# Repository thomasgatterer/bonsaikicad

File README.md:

# bonsaikicad

Hier die (pädagogisch vereinfachte) Simulation des Lerncomputers:
https://bonsai.pinyto.de/

Und hier die Seite des Lehrers der das Projekt ins Leben gerufen hat (ist übrigens der Vater vom Programmierer der Simulation):
http://www.hsg-kl.de/faecher/inf/material/bonsai/

Weiterführendes:
https://tams-www.informatik.uni-hamburg.de/applets/baukasten/DA/VNR_Einleitung.html
www.saar.de/~awa/data/Von-Neumann-Rechner.pdf
informatik-erleben.aau.at/einheiten/uebersicht.php?id0d3

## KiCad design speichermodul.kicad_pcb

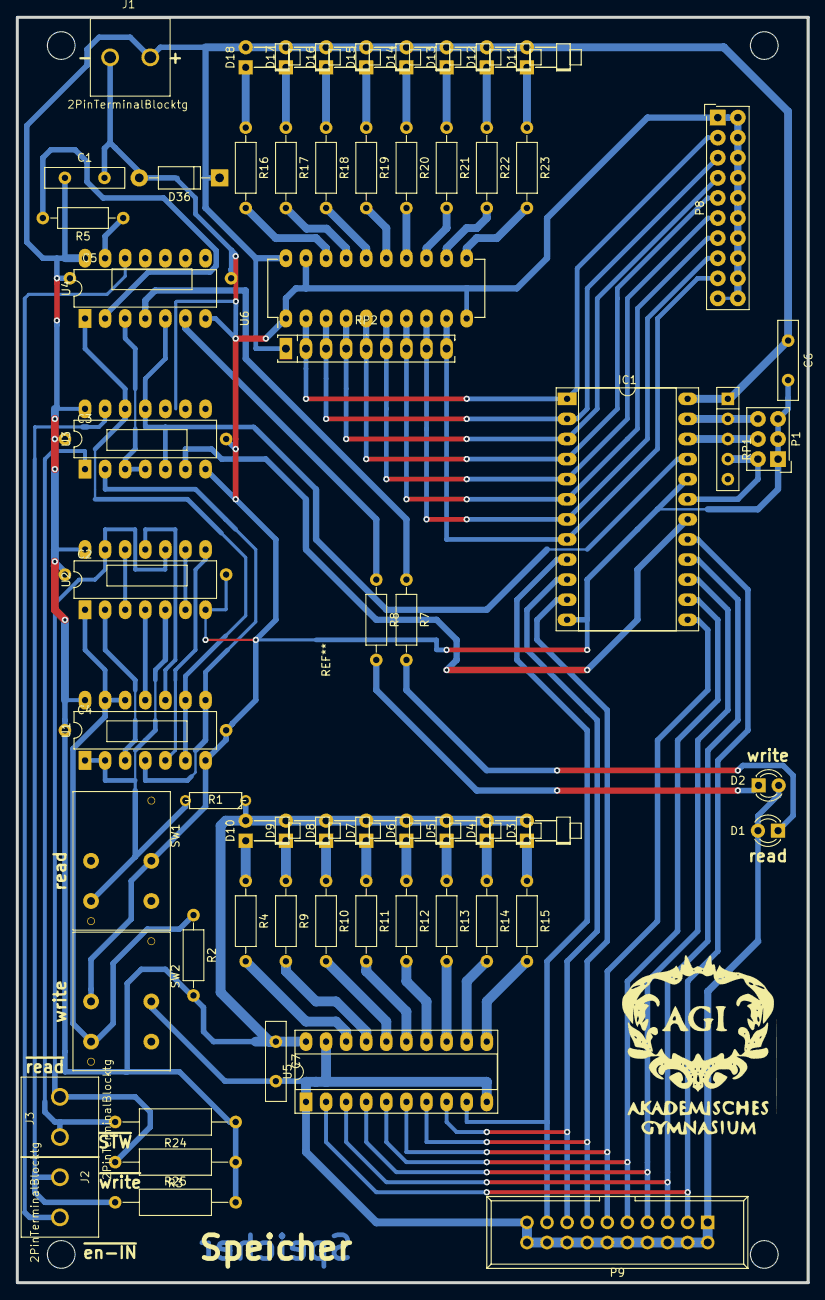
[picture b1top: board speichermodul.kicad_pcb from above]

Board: 2 copper layers, 100.0 x 160.0 mm, 67 parts (0 on the bottom side), 76 nets.

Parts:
C1, C6, C7: 100n; C_Disc_D10.0mm_W2.5mm_P5.00mm
C2, C3, C4, C5: 100n; yyDisc_D10.0mm_W2.5mm_P.00mm
D1, D2: LED; LED_D3.0mm
D3, D4, D5, D6, D7, D8, D9, D10, D11, D12, D13, D14, D15, D16, D17, D18: LED; LED_D1.8mm_W1.8mm_H2.4mm_Horizontal_O3.81mm_Z8.2mm
D36: D; D_DO-41_SOD81_P10.16mm_Horizontal
IC1: 6116; DIP-24_W15.24mm_Socket_LongPads
J1, J2, J3: 2PinTerminalBlocktg
P1: CONN_3X2; SDL-106-X-XX_2x03
P8: CONN_02X10; SDL-120-X-XX_2x10
P9: CONN_02X10; IDC_Header_Straight_20pins
R1: 1,7k; R3
R2: 4,7k; R_Axial_DIN0207_L6.3mm_D2.5mm_P10.16mm_Horizontal
R3, R24, R25: 4,7k; R_Axial_DIN0309_L9.0mm_D3.2mm_P15.24mm_Horizontal
R4, R9, R10, R11, R12, R13, R14, R15, R16, R17, R18, R19, R20, R21, R22, R23: 330; R_Axial_DIN0207_L6.3mm_D2.5mm_P10.16mm_Horizontal
R5: 0; R_Axial_DIN0207_L6.3mm_D2.5mm_P10.16mm_Horizontal
R7, R8: R; R_Axial_DIN0207_L6.3mm_D2.5mm_P10.16mm_Horizontal
RP1: R_PACK4BUSSED; R_Array_SIP5
RP2: R_PACK8BUSSED; SIP9_Housing_BigPads
SW1, SW2: SW_PUSH-tg; SW_PUSH_LCD_E3_SAxxxx_tg_V2
U1: 7400; DIP-14_W7.62mm_LongPads
U2, U3: 74LS08; DIP-14_W7.62mm_LongPads
U4: 74LS14; DIP-14_W7.62mm_LongPads
U5: 74LS540; DIP-20_W7.62mm_Socket_LongPads
U6: 74LS540; DIP-20_W7.62mm_LongPads

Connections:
/A0: IC1.1, P8.3, RP2.2, U6.2
/A1: IC1.2, P8.5, RP2.3, U6.3
/A2: IC1.3, P8.7, RP2.4, U6.4
/A3: IC1.4, P8.9, RP2.5, U6.5
/A4: IC1.5, P8.11, RP2.6, U6.6
/A5: IC1.6, P8.13, RP2.7, U6.7
/A6: IC1.7, P8.15, RP2.8, U6.8
/A7: IC1.8, P8.17, RP2.9, U6.9
/A8: IC1.23, P1.2, RP1.2
/A9: IC1.22, P1.4, RP1.3
/A10: IC1.19, P1.6, RP1.4
/D0: IC1.17, P9.3, U5.2
/D1: IC1.16, P9.5, U5.3
/D2: IC1.15, P9.7, U5.4
/D3: IC1.14, P9.9, U5.5
/D4: IC1.13, P9.11, U5.6
/D5: IC1.11, P9.13, U5.7
/D6: IC1.10, P9.15, U5.8
/D7: IC1.9, P9.17, U5.9
AUTO: J3.2, R3.2, U2.10, U2.13
EN: J2.2, U4.12
GND: C1.2, C2.2, C3.2, C4.2, C5.2, C6.2, C7.2, D1.2, D2.2, D36.2, IC1.12, IC1.20, J1.1, P1.1, P1.3, P1.5, P8.1, P8.2, P8.4, P8.6, P8.8, P8.10, P8.12, P8.14, P8.16, P8.18, P8.19, P8.20, P9.1, P9.2, P9.4, P9.6, P9.8, P9.10, P9.12, P9.14, P9.16, P9.18, P9.19, P9.20, SW1.0, SW2.0, U1.7, U2.7, U3.7, U4.7, U5.1, U5.10, U5.19, U6.1, U6.10, U6.19
unnamed: D1.1, R7.2
unnamed: D2.1, R8.2
unnamed: D3.1, R15.1
unnamed: D4.1, R14.1
unnamed: D5.1, R13.1
unnamed: D6.1, R12.1
unnamed: D7.1, R11.1
unnamed: D8.1, R10.1
unnamed: D9.1, R9.1
unnamed: D10.1, R4.1
unnamed: D11.1, R23.1
unnamed: D12.1, R22.1
unnamed: D13.1, R21.1
unnamed: D14.1, R20.1
unnamed: D15.1, R19.1
unnamed: D16.1, R18.1
unnamed: D17.1, R17.1
unnamed: D18.1, R16.1
unnamed: IC1.18, U3.6
unnamed: IC1.21, U3.5, U3.11, U4.5
unnamed: R1.2, SW1.1, U1.1, U1.2, U2.5
unnamed: R2.1, SW2.1, U1.12, U1.13, U2.1
unnamed: R4.2, U5.18
unnamed: R5.1, U4.13
unnamed: R5.2, U4.2
unnamed: R7.1, U4.4
unnamed: R8.1, U4.6
unnamed: R9.2, U5.17
unnamed: R10.2, U5.16
unnamed: R11.2, U5.15
unnamed: R12.2, U5.14
unnamed: R13.2, U5.13
unnamed: R14.2, U5.12
unnamed: R15.2, U5.11
unnamed: R16.2, U6.18
unnamed: R17.2, U6.17
unnamed: R18.2, U6.16
unnamed: R19.2, U6.15
unnamed: R20.2, U6.14
unnamed: R21.2, U6.13
unnamed: R22.2, U6.12
unnamed: R23.2, U6.11
unnamed: U1.3, U2.2
unnamed: U1.4, U1.8, U3.2
unnamed: U1.5, U2.8
unnamed: U1.6, U1.9, U3.12, U4.1
unnamed: U1.10, U2.11
unnamed: U1.11, U2.4
unnamed: U2.6, U2.9
unnamed: U2.3, U2.12
unnamed: U3.3, U3.4, U4.3
RD: J3.1, R24.2, U3.1
VCC: C1.1, C2.1, C3.1, C4.1, C5.1, C6.1, C7.1, D3.2, D4.2, D5.2, D6.2, D7.2, D8.2, D9.2, D10.2, D11.2, D12.2, D13.2, D14.2, D15.2, D16.2, D17.2, D18.2, D36.1, IC1.24, J1.2, R1.1, R2.2, R3.1, R24.1, R25.2, RP1.1, RP2.1, U1.14, U2.14, U3.14, U4.14, U5.20, U6.20
WR: J2.1, R25.1, U3.13

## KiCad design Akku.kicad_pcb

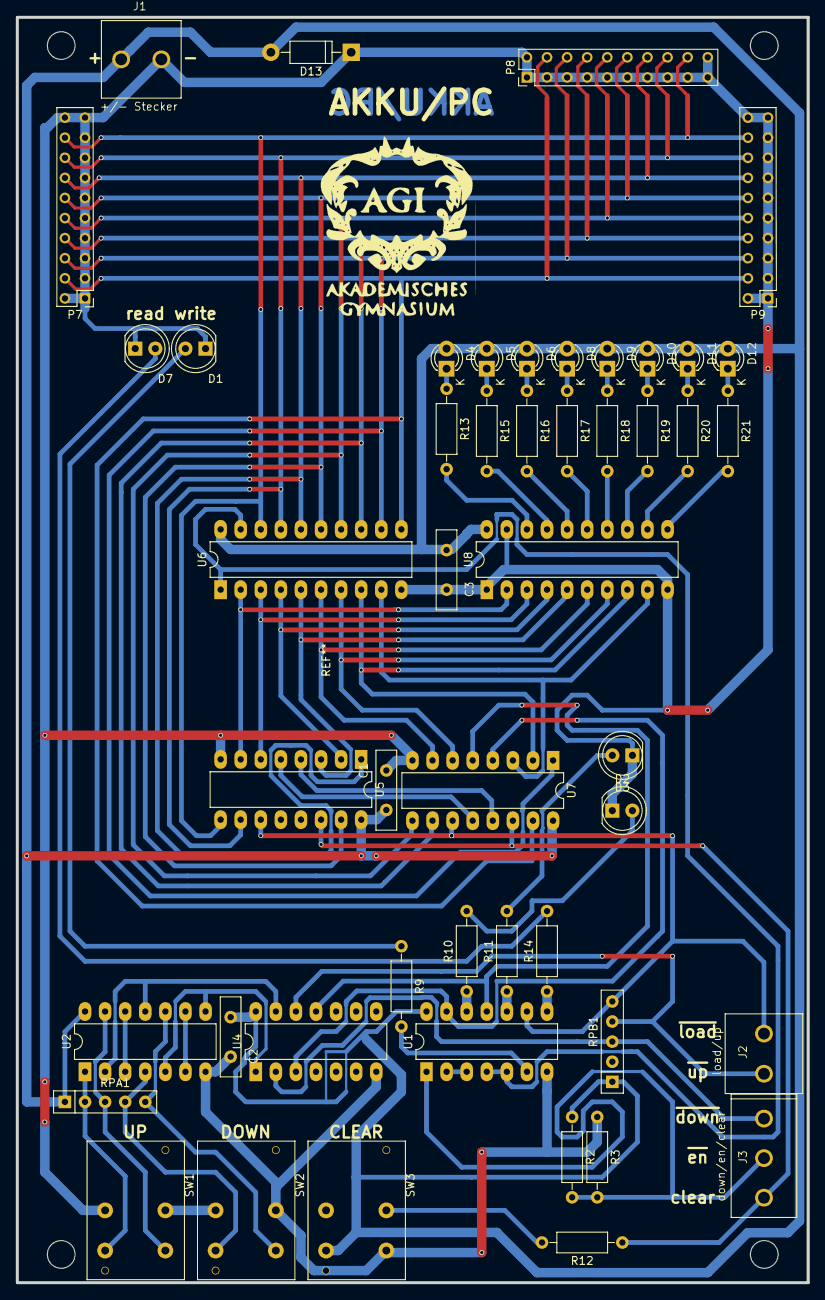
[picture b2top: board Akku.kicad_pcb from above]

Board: 2 copper layers, 100.0 x 160.0 mm, 49 parts (0 on the bottom side), 62 nets.

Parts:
C1, C2, C3: C; C_Disc_D10.0mm_W2.5mm_P5.00mm
D1, D2, D3, D7: LED; LED_D5.0mm_FlatTop
D4, D5, D6, D8, D9, D10, D11, D12: LED; LED-3MM
D13: D; D_DO-41_SOD81_P10.16mm_Horizontal
J1: +/- Stecker; 2PinTerminalBlocktg
J2: load/up; 2PinTerminalBlocktg
J3: down/en/clear; 3PinTerminalBlocktg
P7, P8, P9: CONN_02X10; Pin_Header_Straight_2x10_Pitch2.00mmBonsai.pretty
R2, R3, R9, R10, R11, R12, R13, R14, R15, R16, R17, R18, R19, R20, R21: R; R_Axial_DIN0207_L6.3mm_D2.5mm_P10.16mm_Horizontal
RPA1: R_PACK4BUSSED; R_Array_SIP5
RPB1: R_PACK4BUSSED; R_Array_SIP5
SW1: UP_Bonsai_SWITCH_INV; SW_PUSH_LCD_E3_SAxxxx_tg_V2
SW2: DOWN_Bonsai_SWITCH_INV; SW_PUSH_LCD_E3_SAxxxx_tg_V2
SW3: CLR_Bonsai_SWITCH_INV; SW_PUSH_LCD_E3_SAxxxx_tg_V2
U1: 74HC14; DIP-14_W7.62mm_LongPads
U2: 7400; DIP-14_W7.62mm_LongPads
U4: 7408; DIP-14_W7.62mm_LongPads
U5, U7: 74LS193; DIP-16_W7.62mm_LongPads
U6: 74LS541; DIP-20_W7.62mm_LongPads
U8: 74LS540; DIP-20_W7.62mm_LongPads

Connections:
/a0: P7.19, P8.19, P9.19, U5.9, U6.18
/a1: P7.18, P8.18, P9.18, U5.10, U6.17
/a2: P7.17, P8.17, P9.17, U5.1, U6.16
/a3: P7.16, P8.16, P9.16, U5.15, U6.15
/a4: P7.15, P8.15, P9.15, U6.14, U7.9
/a5: P7.14, P8.14, P9.14, U6.13, U7.10
/a6: P7.13, P8.13, P9.13, U6.12, U7.1
/a7: P7.12, P8.12, P9.12, U6.11, U7.15
CLR: J3.3, R12.1, U5.14, U7.14
GND: C1.1, C2.1, C3.1, D1.1, D2.1, D3.1, D7.1, D13.1, J1.2, P7.1, P7.2, P7.3, P7.4, P7.5, P7.6, P7.7, P7.8, P7.9, P7.10, P7.11, P7.20, P8.1, P8.2, P8.3, P8.4, P8.5, P8.6, P8.7, P8.8, P8.9, P8.10, P8.11, P8.20, P9.1, P9.2, P9.3, P9.4, P9.5, P9.6, P9.7, P9.8, P9.9, P9.10, P9.11, P9.20, R3.1, SW1.0, SW2.0, SW3.2, SW3.6, U1.7, U2.7, U4.7, U5.8, U6.10, U7.8, U8.1, U8.10, U8.19
unnamed: D1.2, R9.1
unnamed: D2.2, R10.2
unnamed: D3.2, R11.2
unnamed: D4.1, R13.1
unnamed: D5.1, R15.1
unnamed: D6.1, R16.1
unnamed: D7.2, R14.2
unnamed: D8.1, R17.1
unnamed: D9.1, R18.1
unnamed: D10.1, R19.1
unnamed: D11.1, R20.1
unnamed: D12.1, R21.1
unnamed: R9.2, U1.6
unnamed: R10.1, U1.12
unnamed: R11.1, U1.10
unnamed: R12.2, SW3.0
unnamed: R13.2, U8.18
unnamed: R14.1, U1.8
unnamed: R15.2, U8.17
unnamed: R16.2, U8.16
unnamed: R17.2, U8.15
unnamed: R18.2, U8.14
unnamed: R19.2, U8.13
unnamed: R20.2, U8.12
unnamed: R21.2, U8.11
unnamed: U1.2, U1.3
unnamed: U1.4, U1.5, U6.1, U6.19
unnamed: U1.11, U4.11, U7.5
unnamed: U1.13, U4.3, U7.4
unnamed: U2.5, U2.8, U4.1
unnamed: U2.6, U2.9
unnamed: U2.2, U2.11, U4.13
unnamed: U2.3, U2.12
unnamed: U5.2, U6.4, U8.4
unnamed: U5.3, U6.5, U8.5
unnamed: U5.4, U7.13
unnamed: U5.5, U7.12
unnamed: U5.6, U6.3, U8.3
unnamed: U5.7, U6.2, U8.2
unnamed: U6.6, U7.7, U8.6
unnamed: U6.7, U7.6, U8.7
unnamed: U6.8, U7.2, U8.8
unnamed: U6.9, U7.3, U8.9
RPA1: RPA1.2, SW1.1, U2.1
RPA2: RPA1.3, SW1.2, U2.13
RPA3: RPA1.4, SW2.1, U2.4
RPA4: RPA1.5, SW2.2, U2.10
RPB2: J3.1, RPB1.3, U4.2
RPB3: J2.2, RPB1.4, U4.12
RPB4: J2.1, RPB1.5, U1.9, U5.11, U7.11
VCC: C1.2, C2.2, C3.2, D4.2, D5.2, D6.2, D8.2, D9.2, D10.2, D11.2, D12.2, D13.2, J1.1, R2.1, RPA1.1, RPB1.1, SW3.1, U1.14, U2.14, U4.14, U5.16, U6.20, U7.16, U8.20
^enable: J3.2, R2.2, R3.2, U1.1

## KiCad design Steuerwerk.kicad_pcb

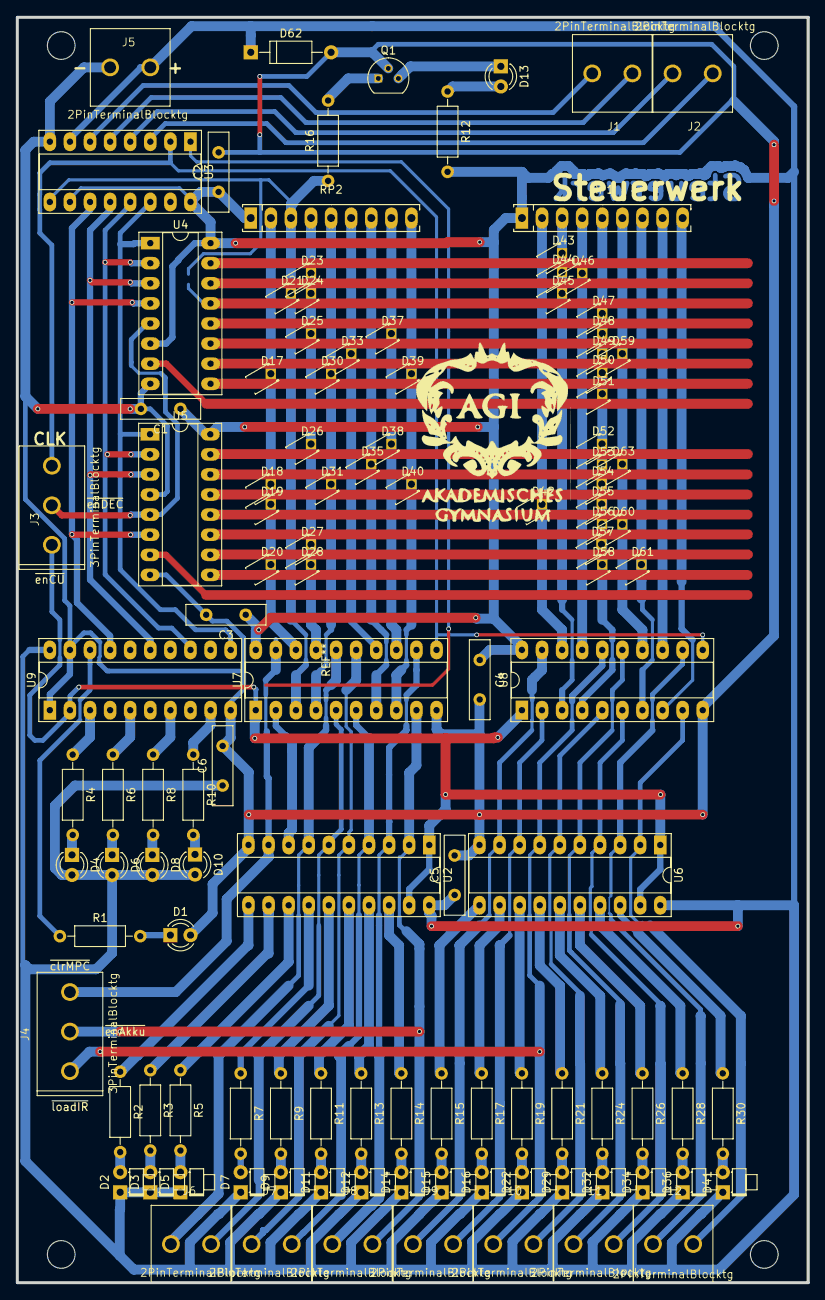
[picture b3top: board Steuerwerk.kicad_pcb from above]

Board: 2 copper layers, 100.0 x 160.0 mm, 115 parts (0 on the bottom side), 104 nets.

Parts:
C1, C2, C3, C4, C5, C6: 100n; C_Disc_D10.0mm_W2.5mm_P5.00mm
D1, D4, D6, D8, D10, D13: LED; LED_D3.0mm
D2, D3, D5, D7, D9, D11, D12, D14, D15, D16, D22, D29, D32, D34, D36, D41: LED; LED_D1.8mm_W1.8mm_H2.4mm_Horizontal_O1.27mm_Z1.6mm
D17, D18, D19, D20, D21, D23, D24, D25, D26, D27, D28, D30, D31, D33, D35, D37, D38, D39, D40, D42, D43, D44, D45, D46, D47, D48, D49, D50, D51, D52, D53, D54, D55, D56, D57, D58, D59, D60, D61, D63: Led_Small; LED_D1.8mm_W3.3mm_H2.4mmBonsai
D62: D; D_A-405_P10.16mm_Horizontal
J1, J2, J5, J6, J7, J8, J9, J10, J11, J12: 2PinTerminalBlocktg
J3, J4: 3PinTerminalBlocktg
Q1: Q_PNP_BCE; TO-92_Molded_Narrow
R1, R2, R3, R4, R5, R6, R7, R8, R9, R10, R11, R12, R13, R14, R15, R16, R17, R19, R21, R24, R26, R28, R30: R; R_Axial_DIN0207_L6.3mm_D2.5mm_P10.16mm_Horizontal
RP1, RP2: R_PACK8BUSSED; SIP9_Housing_BigPads
U2, U6: 74541; DIP-20_W7.62mm_Socket_LongPads
U3: 74LS161; DIP-16_W7.62mm_Socket_LongPads
U4, U5: 74LS138; DIP-16_W7.62mm_Socket_LongPads
U7: 74LS374; DIP-20_W7.62mm_Socket_LongPads
U8: 74LS374; DIP-20_W7.62mm_Socket_LongPadstg
U9: 74ls240; DIP-20_W7.62mm_Socket_LongPads

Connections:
/3: J6.1, U2.7, U7.16
/5: J7.1, U2.5, U7.15
/7: J8.1, U2.3, U7.12
/9: J9.1, U6.9, U8.19
/11: J4.1, J10.1, U6.7, U8.16
/13: J11.1, U6.5, U8.15
/15: J12.1, U6.3, U8.12
/16: J12.2, U6.2, U8.9
/Takt: J3.3, U3.2, U7.11, U8.11
/a1: D17.1, D18.1, D19.1, D20.1, RP2.2, U7.18
/a2: D21.1, R16.1, RP2.3, U3.9, U7.3
/a3: D23.1, D24.1, D25.1, D26.1, D27.1, D28.1, RP2.4, U7.17
/a4: D30.1, D31.1, RP2.5, U7.4
/a5: D33.1, RP2.6, U7.14
/a6: D35.1, RP2.7, U7.7
/a7: D37.1, D38.1, RP2.8, U7.13
/a8: D39.1, D40.1, RP2.9, U7.8
/b1: D42.1, RP1.2, U8.18
/b2: D43.1, D44.1, D45.1, RP1.3, U8.3
/b3: D46.1, RP1.4, U8.17
/b4: D47.1, D48.1, D49.1, D50.1, D51.1, D52.1, D53.1, D54.1, D55.1, D56.1, D57.1, D58.1, RP1.5, U8.4
/b5: D59.1, D60.1, D63.1, RP1.6, U8.14
/b6: D61.1, RP1.7, U8.7
/b7: RP1.8, U8.13
/b8: RP1.9, U8.8
/clrMPC: J4.3, U2.9, U3.1, U7.19
/enAkku: J4.2, J8.2, U2.2, U7.9
/enDEC: J3.2, U4.5, U5.5
/enSTW: J3.1, U2.1, U2.19, U6.1, U6.19, U7.1, U8.1, U9.2
GND: C1.2, C2.2, C3.2, C4.2, C5.2, C6.2, D1.2, D62.2, J5.1, Q1.2, U2.10, U3.8, U4.8, U5.4, U5.8, U6.10, U7.10, U8.10, U9.1, U9.10, U9.19
unnamed: D1.1, R1.2
unnamed: D2.2, R2.2
unnamed: D3.2, R3.2
unnamed: D4.1, R4.2
unnamed: D5.2, R5.2
unnamed: D6.1, R6.2
unnamed: D7.2, R7.2
unnamed: D8.1, R8.2
unnamed: D9.2, R9.2
unnamed: D10.1, R10.2
unnamed: D11.2, R11.2
unnamed: D12.2, R13.2
unnamed: D13.1, Q1.3
unnamed: D13.2, R12.1
unnamed: D14.2, R14.2
unnamed: D15.2, R15.2
unnamed: D16.2, R17.2
unnamed: D17.2, D30.2, D39.2, D50.2, U4.9
unnamed: D18.2, D31.2, D40.2, D54.2, U5.13
unnamed: D19.2, D42.2, D55.2, U5.12
unnamed: D20.2, D28.2, D58.2, D61.2, U5.9
unnamed: D21.2, D24.2, D45.2, U4.13
unnamed: D22.2, R19.2
unnamed: D23.2, D44.2, D46.2, U4.14
unnamed: D25.2, D37.2, D48.2, U4.11
unnamed: D26.2, D38.2, D52.2, U5.15
unnamed: D27.2, D57.2, U5.10
unnamed: D29.2, R21.2
unnamed: D32.2, R24.2
unnamed: D33.2, D49.2, D59.2, U4.10
unnamed: D34.2, R26.2
unnamed: D35.2, D53.2, D63.2, U5.14
unnamed: D36.2, R28.2
unnamed: D41.2, R30.2
unnamed: D43.2, U4.15
unnamed: D47.2, U4.12
unnamed: D51.2, U4.7
unnamed: D56.2, D60.2, U5.11
unnamed: J1.1, U3.5
unnamed: J1.2, U3.6
unnamed: J2.1, U3.3
unnamed: J2.2, U3.4
unnamed: J6.2, U2.6, U7.5
unnamed: J7.2, U2.4, U7.6
unnamed: J9.2, U6.8, U8.2
unnamed: J10.2, U6.6, U8.5
unnamed: J11.2, U6.4, U8.6
unnamed: Q1.1, R16.2
unnamed: R1.1, U9.18
unnamed: R2.1, U2.11
unnamed: R3.1, U2.12
unnamed: R4.1, U9.3
unnamed: R5.1, U2.13
unnamed: R6.1, U9.5
unnamed: R7.1, U2.14
unnamed: R8.1, U9.7
unnamed: R9.1, U2.15
unnamed: R10.1, U9.9
unnamed: R11.1, U2.16
unnamed: R13.1, U2.17
unnamed: R14.1, U2.18
unnamed: R15.1, U6.11
unnamed: R17.1, U6.12
unnamed: R19.1, U6.13
unnamed: R21.1, U6.14
unnamed: R24.1, U6.15
unnamed: R26.1, U6.16
unnamed: R28.1, U6.17
unnamed: R30.1, U6.18
unnamed: U3.11, U4.4, U5.6, U9.17
unnamed: U3.12, U4.3, U5.3, U9.15
unnamed: U3.13, U4.2, U5.2, U9.13
unnamed: U3.14, U4.1, U5.1, U9.11
VCC: C1.1, C2.1, C3.1, C4.1, C5.1, C6.1, D2.1, D3.1, D4.2, D5.1, D6.2, D7.1, D8.2, D9.1, D10.2, D11.1, D12.1, D14.1, D15.1, D16.1, D22.1, D29.1, D32.1, D34.1, D36.1, D41.1, D62.1, J5.2, R12.2, RP1.1, RP2.1, U2.20, U3.7, U3.10, U3.16, U4.6, U4.16, U5.16, U6.20, U7.20, U8.20, U9.20

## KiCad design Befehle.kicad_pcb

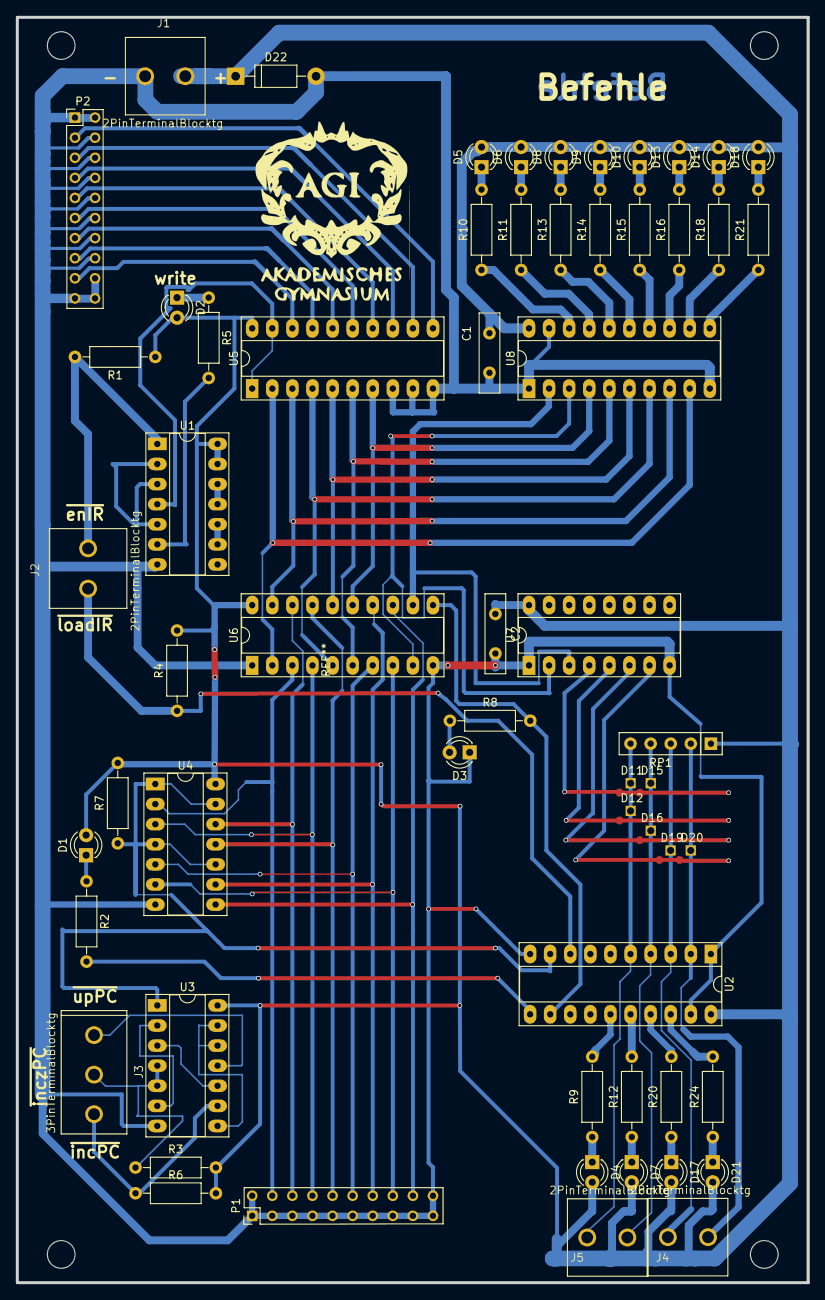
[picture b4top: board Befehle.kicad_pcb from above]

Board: 2 copper layers, 100.0 x 160.0 mm, 60 parts (0 on the bottom side), 77 nets.

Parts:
C1, C2: 100n; C_Disc_D10.0mm_W2.5mm_P5.00mm
D1, D3, D4, D7, D17, D18, D21: LED; LED_D3.0mm
D2, D5, D6, D8, D9, D10, D13, D14: Led_Small; LED_D3.0mm
D11, D12, D15, D16, D19, D20: Led_Small; Diode_D1.8mm_W3.3mm_H2.4mmBonsai
D22: D; D_DO-41_SOD81_P10.16mm_Horizontal
J1, J2, J4, J5: 2PinTerminalBlocktg
J3: 3PinTerminalBlocktg
P1, P2: CONN_02X10; Pin_Header_Straight_2x10_Pitch2.00mmBonsai.pretty
R1, R3, R4, R6: 4,7k; R_Axial_DIN0207_L6.3mm_D2.5mm_P10.16mm_Horizontal
R2, R5, R8, R9, R10, R11, R12, R13, R14, R15, R16, R18, R20, R21, R24: 330; R_Axial_DIN0207_L6.3mm_D2.5mm_P10.16mm_Horizontal
R7: 1k; R_Axial_DIN0207_L6.3mm_D2.5mm_P10.16mm_Horizontal
RP1: R_PACK4BUSSED; R_Array_SIP5
U1: 74LS14; DIP-14_W7.62mm_Socket_LongPadstg
U2: 74540; DIP-20_W7.62mm_Socket_LongPadstg
U3: 7400; DIP-14_W7.62mm_Socket_LongPadstg
U4: 74HCT02; DIP-14_W7.62mm_Socket_LongPadstg
U5: 74LS541; DIP-20_W7.62mm_Socket_LongPadstg
U6: 74LS373; DIP-20_W7.62mm_Socket_LongPadstg
U7: 74LS139; DIP-16_W7.62mm_Socket_LongPadstg
U8: 74LS540; DIP-20_W7.62mm_Socket_LongPadstg

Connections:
0: D20.1, J4.1, RP1.2, U2.2
1: D19.1, J4.2, RP1.3, U2.3
2: D15.1, D16.1, J5.1, RP1.4, U2.4
3: D11.1, D12.1, J5.2, RP1.5, U2.5
/a1: U5.2, U6.2, U8.9
/a2: U5.3, U6.19, U8.8
/a3: U5.4, U6.5, U8.7
/a4: U6.12, U7.3, U8.2
/a5: U5.6, U6.6, U8.5
/a6: U5.7, U6.15, U8.4
/a7: U6.9, U7.2, U8.3
/a8: U5.5, U6.16, U8.6
/d1: P1.13, U4.12, U6.18
/d2: P1.12, U4.2, U6.3
/d3: P1.15, U4.11, U6.17
/d4: P1.19, U4.8, U6.13
/d5: P1.17, U4.9, U6.14
/d6: P1.18, U4.6, U6.8
/d7: P1.14, U4.3, U6.4
/d44: P1.16, U4.5, U6.7
GND: C1.2, C2.2, D3.1, D22.2, J1.1, P1.1, P1.2, P1.3, P1.4, P1.5, P1.6, P1.7, P1.8, P1.9, P1.10, P1.11, P1.20, P2.1, P2.10, P2.11, P2.12, P2.13, P2.14, P2.15, P2.16, P2.17, P2.18, P2.19, P2.20, U1.7, U2.1, U2.10, U2.19, U3.7, U4.7, U5.8, U5.9, U5.10, U6.1, U6.10, U7.1, U7.8, U8.1, U8.10, U8.19
unnamed: D1.1, R2.1
unnamed: D2.1, R5.1
unnamed: D3.2, R8.1
unnamed: D4.1, R9.1
unnamed: D5.1, R10.2
unnamed: D6.1, R11.2
unnamed: D7.1, R12.1
unnamed: D8.1, R13.2
unnamed: D9.1, R14.2
unnamed: D10.1, R15.2
unnamed: D11.2, D15.2, U7.4
unnamed: D12.2, U7.5
unnamed: D13.1, R16.2
unnamed: D14.1, R18.2
unnamed: D16.2, U7.6
unnamed: D17.1, R20.1
unnamed: D18.1, R21.2
unnamed: D19.2, D20.2, U7.7
unnamed: D21.1, R24.1
unnamed: P2.2, U5.11
unnamed: P2.3, U5.12
unnamed: P2.4, U5.13
unnamed: P2.5, U5.14
unnamed: P2.6, U5.15
unnamed: P2.7, U5.16
unnamed: P2.8, U5.17
unnamed: P2.9, U5.18
unnamed: R2.2, U2.11
unnamed: R5.2, U1.6
unnamed: R7.1, U2.9, U3.1, U4.1, U4.4, U4.10, U4.13
unnamed: R8.2, U2.12, U6.11
unnamed: R9.2, U2.15
unnamed: R10.1, U8.18
unnamed: R11.1, U8.17
unnamed: R12.2, U2.16
unnamed: R13.1, U8.16
unnamed: R14.1, U8.15
unnamed: R15.1, U8.14
unnamed: R16.1, U8.13
unnamed: R18.1, U8.12
unnamed: R20.2, U2.17
unnamed: R21.1, U8.11
unnamed: R24.2, U2.18
unnamed: U1.2, U1.3, U1.5
unnamed: U1.4, U5.1, U5.19
unnamed: U1.9, U1.10
unnamed: U1.11, U1.12
unnamed: U3.2, U3.6
unnamed: U3.3, U3.10
unnamed: U3.8, U3.12, U3.13
VCC: C1.1, C2.1, D1.2, D2.2, D4.2, D5.2, D6.2, D7.2, D8.2, D9.2, D10.2, D13.2, D14.2, D17.2, D18.2, D21.2, D22.1, J1.2, R1.1, R3.2, R4.2, R6.2, R7.2, RP1.1, U1.13, U1.14, U2.20, U3.14, U4.14, U5.20, U6.20, U7.16, U8.20
enableR: J2.2, R1.2, U1.1
incPC: J3.3, R6.1, U3.9
incPCz: J3.2, R3.1, U3.4, U3.5
loadIR: J2.1, R4.1, U2.8
upPC: J3.1, U3.11

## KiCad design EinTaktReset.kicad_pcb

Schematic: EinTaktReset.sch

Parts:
C1: 47µ; CP_Radial_D5.0mm_P2.00mm
C2: 10 µ; CP_Radial_D5.0mm_P2.00mm
C3: 220 µ; CP_Radial_D8.0mm_P3.50mm
C4: 220µ; CP_Radial_D8.0mm_P3.50mm
C5: 10n; C_Disc_D3.0mm_W1.6mm_P2.50mm
C6, C7, C8, C9: 100n; C_Disc_D10.0mm_W2.5mm_P5.00mm
D1, D3: D; D_DO-35_SOD27_P10.16mm_Horizontal
D2: LED; LED_D5.0mm
DROT1: LED; LED_D3.0mm
IC1: 74LS624; DIP-14_W7.62mm_Socket_LongPads
J1, J2, J4: 3PinTerminalBlocktg
J3, J5: 2PinTerminalBlocktg
P1, P4: CONN_02X10; Pin_Header_Straight_2x10_Pitch2.00mmBonsai.pretty
R1, R17: 10k; R_Axial_DIN0207_L6.3mm_D2.5mm_P10.16mm_Horizontal
R2: 100; R_Axial_DIN0207_L6.3mm_D2.5mm_P10.16mm_Horizontal
R3: 10k; R_Axial_DIN0207_L6.3mm_D2.5mm_P17.7mm_Horizontaltg
R4: 150; R_Axial_DIN0207_L6.3mm_D2.5mm_P10.16mm_Horizontal
R5, R6: 470; R_Axial_DIN0207_L6.3mm_D2.5mm_P10.16mm_Horizontal
R7: 330; R_Axial_DIN0207_L6.3mm_D2.5mm_P21.59mm_Horizontaltg
R8: 1,8k; R_Axial_DIN0207_L6.3mm_D2.5mm_P10.16mm_Horizontal
R9: 2,2k; R_Axial_DIN0207_L6.3mm_D2.5mm_P12.7mm_Horizontaltg
R10, R11, R14, R15, R16: 4,7k; R_Axial_DIN0207_L6.3mm_D2.5mm_P10.16mm_Horizontal
R12: 1,8k; R_Axial_DIN0207_L6.3mm_D2.5mm_P12.7mm_Horizontaltg
R13: 2,2k; R_Axial_DIN0207_L6.3mm_D2.5mm_P10.16mm_Horizontal
RP1: R_PACK8BUSSED; SIP9_Housing_BigPads
RV1: POT; Potentiometer_Trimmer_Piher_PT-10v5_Horizontal_Px5.0mm_Py5.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
SW1, SW2: SWITCH_INV; SW_PUSH_LCD_E3_SAxxxx_tg_V2
SW3, SW4, SW5, SW7, SW8, SW9, SW10, SW11, SW12, SW13: SPST; eintakt_tg_SW_CuK_JS202011CQN_DPDT_Straight
SW6: SWITCH_INV; eintakt_tg_SW_CuK_JS202011CQN_DPDT_Straight
U1: 74LS132; DIP-14_W7.62mm_Socket_LongPads
U2: 74540En; DIP-20_W7.62mm_Socket_LongPads
U3: 74HCT541_PWR; DIP-20_W7.62mm_Socket_LongPads
U4: 74LS32; DIP-14_W7.62mm_Socket_LongPads
U5: 74LS00; DIP-14_W7.62mm_Socket_LongPads

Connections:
/a0: P1.2, P4.2, U3.18
/a1: P1.3, P4.3, U3.17
/a2: P1.4, P4.4, U3.16
/a3: P1.5, P4.5, U3.15
/a4: P1.6, P4.6, U3.14
/a5: P1.7, P4.7, U3.13
/a6: P1.8, P4.8, U3.12
/a7: P1.9, P4.9, U3.11
CLK: J2.1, U4.9, U4.10, U4.11
GND: C1.2, C2.2, C6.2, C7.2, C8.2, C9.2, D3.2, IC1.1, IC1.7, J3.1, P1.1, P1.10, P1.11, P1.12, P1.13, P1.14, P1.15, P1.16, P1.17, P1.18, P1.19, P1.20, P4.1, P4.10, P4.11, P4.12, P4.13, P4.14, P4.15, P4.16, P4.17, P4.18, P4.19, P4.20, R4.2, R5.2, R9.1, R13.1, RV1.3, SW1.0, SW2.0, SW3.1, SW5.1, SW6.2, SW7.1, SW8.1, SW9.1, SW10.1, SW11.1, SW12.1, SW13.1, U1.7, U2.10, U3.10, U4.7, U5.7
unnamed: C1.1, R2.2
unnamed: C2.1, R3.2, U2.9
unnamed: C3.1, C4.1
unnamed: C3.2, SW4.2
unnamed: C4.2, C5.1, IC1.4
unnamed: C5.2, IC1.3, SW4.1
unnamed: D1.2, R1.2, R2.1, SW1.1, U1.1, U1.2
unnamed: D2.1, R7.2
unnamed: DROT1.1 (K), R4.1
unnamed: DROT1.2 (A), U4.8
unnamed: IC1.2, R17.1
unnamed: IC1.5, R16.2, SW3.2
unnamed: IC1.8, U5.2
unnamed: IC1.13, RV1.2
unnamed: R5.1, U2.5, U2.6
unnamed: R6.1, U2.2, U2.3, U2.4
unnamed: R7.1, U4.3
unnamed: R14.2, SW2.1, U1.13
unnamed: R15.1, SW2.2, U1.9, U2.13
unnamed: RP1.2, SW5.2, U3.2
unnamed: RP1.3, SW7.2, U3.3
unnamed: RP1.4, SW8.2, U3.4
unnamed: RP1.5, SW9.2, U3.5
unnamed: RP1.6, SW10.2, U3.6
unnamed: RP1.7, SW11.2, U3.7
unnamed: RP1.8, SW12.2, U3.8
unnamed: RP1.9, SW13.2, U3.9
unnamed: U1.6, U2.1, U2.19, U5.1
unnamed: U1.10, U1.11
unnamed: U1.8, U1.12, U4.12
unnamed: U2.8, U2.11
unnamed: U2.7, U2.12
unnamed: U3.1, U3.19, U4.1, U4.2, U5.8
unnamed: U4.13, U5.6
unnamed: U5.3, U5.4, U5.5
unnamed: U5.9, U5.10, U5.11
VCC: C6.1, C7.1, C8.1, C9.1, D1.1, D2.2, D3.1, IC1.9, IC1.14, J3.2, R1.1, R3.1, R6.2, R8.2, R10.1, R11.2, R12.2, R14.1, R15.2, R16.1, R17.2, RP1.1, RV1.1, SW6.0, U1.14, U3.20, U4.14, U5.14
auto: J1.3, SW6.1, U4.5
clrAkku: J5.2, U2.14
clrMPC: J4.1, U2.18
clrPC: J5.1, U2.15
en-ln1: J1.1, R11.1, U5.13
en-ln2: J1.2, R10.2, U5.12
enAkku: J4.2, R8.1, R9.2, U2.17
enDEC: J2.2, U1.3, U1.4, U1.5, U4.4
enSTW: J2.3, U4.6
loadIR: J4.3, R12.1, R13.2, U2.16

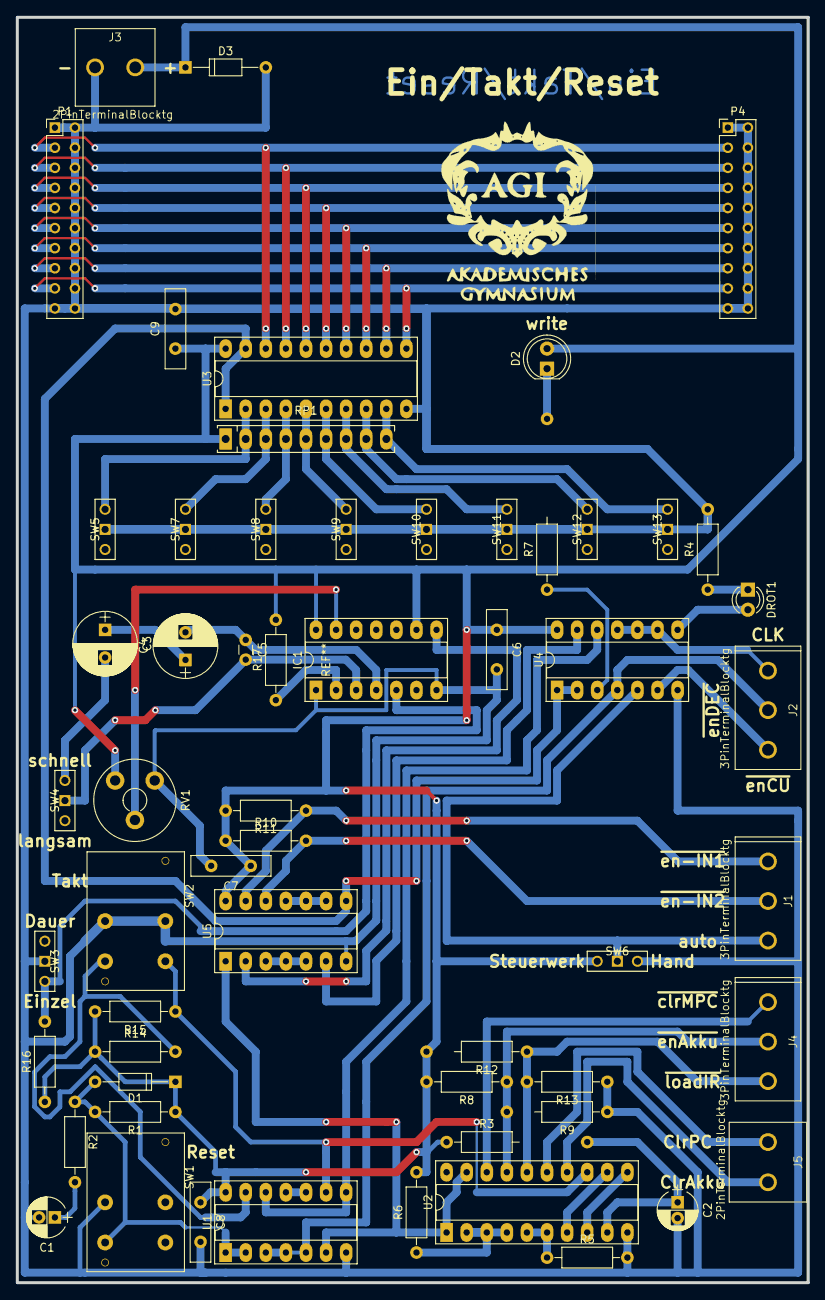
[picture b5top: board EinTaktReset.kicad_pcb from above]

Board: 2 copper layers, 100.0 x 160.0 mm, 58 parts (0 on the bottom side), 57 nets.

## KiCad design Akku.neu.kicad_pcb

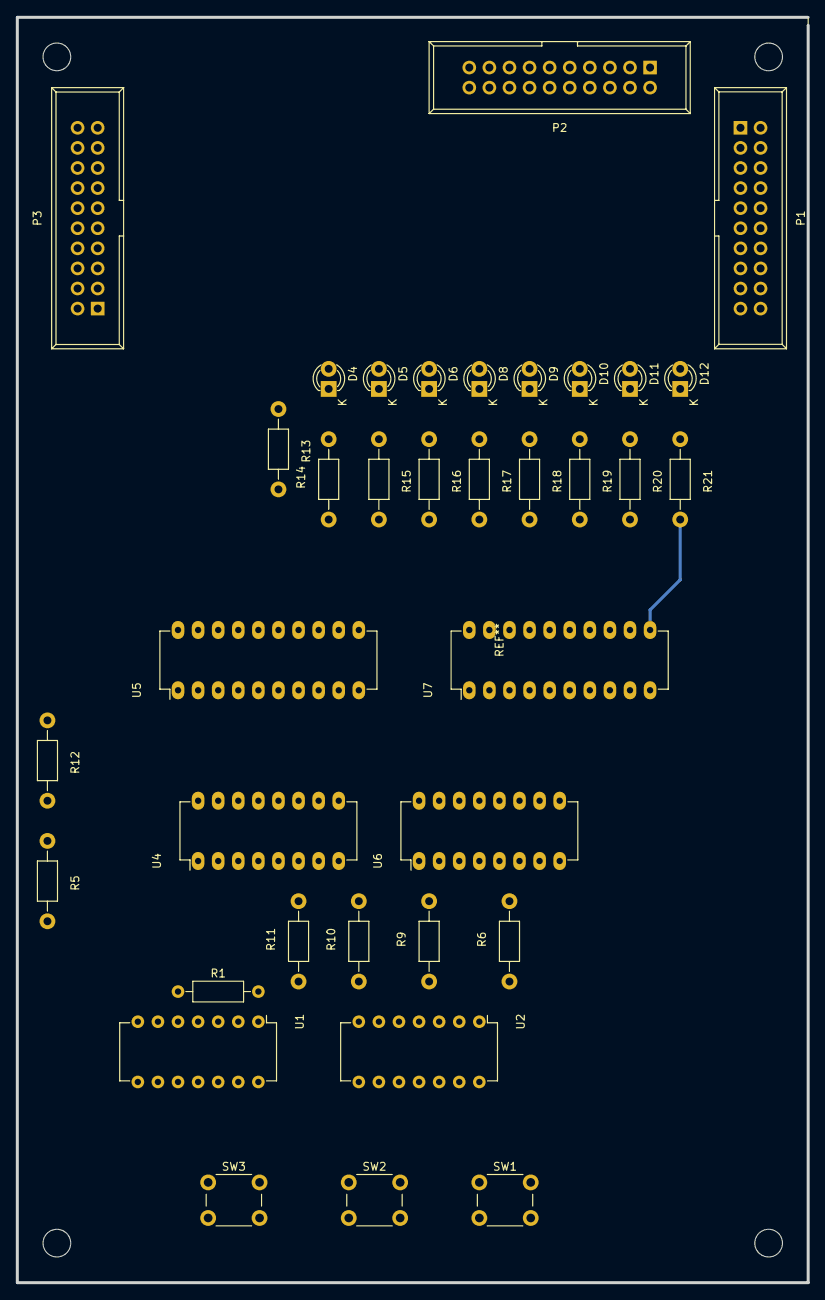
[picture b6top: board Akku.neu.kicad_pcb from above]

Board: 2 copper layers, 100.0 x 160.0 mm, 36 parts (0 on the bottom side), 60 nets.

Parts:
D4, D5, D6, D8, D9, D10, D11, D12: LED; LED-3MM
P1, P2, P3: CONN_02X10; IDC_Header_Straight_20pins
R1: R; R_Axial_DIN0207_L6.3mm_D2.5mm_P10.16mm_Horizontal
R5, R6, R9, R10, R11, R12, R13, R14, R15, R16, R17, R18, R19, R20, R21: R; Resistor_Horizontal_RM10mm
SW1, SW2, SW3: SWITCH_INV; SW_PUSH_6mm_h5mm
U1: 7400; DIP-14_W7.62mm
U2: 7408; DIP-14_W7.62mm
U4, U6: 74LS193; DIP-16_W7.62mm_LongPads
U5: 74LS541; DIP-20_W7.62mm_LongPads
U7: 74LS540; DIP-20_W7.62mm_LongPads

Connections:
/a0: P1.4, P2.4, P3.4
/a1: P1.6, P2.6, P3.6
/a2: P1.8, P2.8, P3.8
/a3: P1.10, P2.10, P3.10
/a4: P1.12, P2.12, P3.12
/a5: P1.14, P2.14, P3.14
/a6: P1.16, P2.16, P3.16
/a7: P1.18, P2.18, P3.18
CLR: R12.1, U4.14, U6.14
GND: R9.2, SW1.2, SW2.2, SW3.1, U1.7, U2.7, U4.8, U5.10, U6.8, U7.1, U7.10, U7.19
unnamed: D4.1, R13.1
unnamed: D5.1, R15.1
unnamed: D6.1, R16.1
unnamed: D8.1, R17.1
unnamed: D9.1, R18.1
unnamed: D10.1, R19.1
unnamed: D11.1, R20.1
unnamed: D12.1, R21.1
unnamed: P1.1, P1.2, P1.3, P1.5, P1.7, P1.9, P1.11, P1.13, P1.15, P1.17, P1.19, P1.20, P2.1, P2.2, P2.3, P2.5, P2.7, P2.9, P2.11, P2.13, P2.15, P2.17, P2.19, P2.20
unnamed: P3.1, P3.2, P3.3, P3.5, P3.7, P3.9, P3.11, P3.13, P3.15, P3.17, P3.19, P3.20
unnamed: R1.2, SW1.1, U1.1
unnamed: SW2.1, U1.12
unnamed: R12.2, SW3.2
unnamed: R13.2, U7.18
unnamed: R15.2, U7.17
unnamed: R16.2, U7.16
unnamed: R17.2, U7.15
unnamed: R18.2, U7.14
unnamed: R19.2, U7.13
unnamed: R20.2, U7.12
unnamed: R21.2, U7.11
unnamed: U1.2, U1.6
unnamed: U1.3, U1.4, U2.2
unnamed: U1.9, U1.11
unnamed: U1.8, U1.13, U2.12
unnamed: U2.3, U4.5
unnamed: U2.11, U4.4
unnamed: U5.1, U5.19
unnamed: U4.1, U5.17
unnamed: U4.2, U5.2, U7.2
unnamed: U4.3, U5.3, U7.3
unnamed: U4.6, U5.5, U7.5
unnamed: U4.7, U5.4, U7.4
unnamed: U4.9, U5.15
unnamed: U4.10, U5.16
unnamed: U4.12, U6.5
unnamed: U4.13, U6.4
unnamed: U4.15, U5.18
unnamed: U5.6, U6.2, U7.6
unnamed: U5.7, U6.3, U7.7
unnamed: U5.8, U6.7, U7.8
unnamed: U5.9, U6.6, U7.9
unnamed: U5.11, U6.9
unnamed: U5.12, U6.10
unnamed: U5.13, U6.1
unnamed: U5.14, U6.15
VCC: D4.2, D5.2, D6.2, D8.2, D9.2, D10.2, D11.2, D12.2, R1.1, R5.1, R6.1, U1.14, U2.14, U4.16, U5.20, U6.16, U7.20
down: R6.2, U2.13
load: U4.11, U6.11
up: R5.2, U2.1

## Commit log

2016-09-09 inital data commit
2016-09-09 additions and corrections
2016-09-10 switch to kicad 4
2016-09-11 trying building new components
2016-09-11 special lib error fixt, new part tests cleaned
2016-09-11 new resistor pack in eeschema
2016-09-11 schematic almoust finished
2016-09-13 schematic completed
2016-09-16 changed version to Nightly Development Build for missing footprints
2016-10-03 AKKU von Simon zum Projekt hinzugefügt
2016-10-10 EinTakt hinzugefügt
2016-10-10 added Steuerwerk
2016-10-10 Akku/PC aktualisiert
2016-10-17 add footprints to speichermodul
2016-10-17 Befehle hinzugfefügt
2016-10-17 Steuerwerk aktualisiert
2016-10-17 Akku aktualisiert
2016-10-24 Akku Schaltplan aktualisiert
2016-10-24 Schaltplan erweitert
2016-11-07 Schaltplan (wie mit T. Gatterer besprochen) fertiggestellt. Annotations. Footprints begonnen.
2016-11-14 Annotierung und Footprints
2016-11-14 Befehle aktualisiert
2016-11-28 Steuerwerk: Footprints
2016-12-05 Akku Schaltplan fast fertiggestellt; PCB angefangen.
2016-12-05 Befehle Speicherplan fast fertig
2016-12-05 Schaltplan weitergeführt
2016-12-12 Footprints Steuerwerk
2016-12-12 Akku/PC PCB verbessert
2016-12-12 Speicher Footprints
2016-12-19 Fehler am Schaltplan ausgebessert; PCB erweitert
2017-02-06 einige DIPs hinzugefügt
2017-02-20 einige Rewistoren hinzugefügt
2017-03-06 Bauteile hinzugefügt
2017-03-13 einige Leds und Resistoren hinzugefügt und ausgebessert
2017-03-13 Footprints ausgebessert und die Positionierung der Bauteile begonnen
2017-03-13 pcb weiter verschobene bauteile
2017-03-20 einige Footprints geändert
2017-03-20 netzlisten neu
2017-03-20 wiederständs arrays überarbeitet
2017-03-20 Befehle Footprints und Leiterbahnen added
2017-11-15 bauteile angeordnet
2017-11-15 Pcb layout geändert
2017-11-22 added lib
2017-11-22 test removed
2017-11-22 Akku.sch verändert, Components ausgetauscht
2017-11-22 Pcb layout und neue footprints eingefügt
2017-11-29 neue Steuerwerk Resistoren mit dateien
2017-11-29 Footprints added
2017-11-29 .sch datei leicht verändert
2017-11-29 Kabel verlegen und pcb layout
2017-11-30 lib 74540 added ACHTUNG: Versionsprobleme checken
2017-12-06 Akku Namen Problem behoben
2017-12-06 changes in eintaktreset .sch
2017-12-10 git config test
2017-12-13 testdatei hinzugefügt zu forked projekt
2017-12-13 Dioden und Anschlüsse
2017-12-13 changes in eintaktres .sch
2017-12-13 beschriftungen organisiert
2017-12-14 "uploadtest"
2017-12-14 reset logic added
2017-12-14 testdatei2 hinzugefügt für pushtest
2017-12-14 bus connections angefangen
2017-12-14 bus improved
2017-12-17 74540 with enable pin added
2017-12-19 Beschriftungen formatiert
2017-12-19 busverbindungen in eintaktreset fertig gezeichnet
2017-12-20 testforcpulls
2017-12-20 fehlende Chips und Komponenten hinzugefügt
2017-12-20 Pcb layout perfektioniert und schaltplan vorangetrieben
2017-12-20 resistors added,label and output pins added
2017-12-20 footprints bearbeitet und geordnet
2017-12-20 Akku.sch fertiggestellt, Footprintfehler behoben, PCB Grundauslegung begonnen
2017-12-22 cleanup: test filses removed
2017-12-22 Version changegit status! footprints, pcb speichermodul
2017-12-22 speichermodul to new version
2017-12-22 Steuerwerk to pcb
2017-12-23 Akku to new kicad version
2017-12-23 befehle.sch to new kicad version
2017-12-23 Eintakt.sch to new kicad version
2017-12-23 Eintakt bugfixing ERC (more or less) done
2017-12-24 part changed 240 in lib added
2017-12-25 74541 output series (south) corrected, tackt, enDec, enSTW, clrMPC, enAkku, laodIR checked
2017-12-25 Steuerwerk: some minor fixes
2017-12-25 Steuerwerk: 74ls161 (nort west) adapted labels and error corrections
2017-12-26 steuerwerk: .sch almost debuged
2017-12-26 steuerwerk: start pcb
2018-01-07 Befehle Footprints and 74540 part order fixed
2018-01-11 names and footprints fixes
2018-01-16 EinTaktReset checked, no ? found
2018-01-16 RPacked 5Pinns in Befehle und Speicher added and some strange fixes (not connected pins ...)
2018-01-16 foodprinting EintaktReset
2018-01-16 foodprinting EintaktReset2
2018-01-17 footprint library added
2018-01-17 footprinting EintaktReset3
2018-01-17 library tmptg... fixtried
2018-01-17 Ordnen der Teile im PCB
2018-01-17 alles neu, also alles
2018-01-17 Footprints bearbeitet
2018-01-17 PCB voll überaqrbeitet
2018-01-17 Speichern
2018-01-21 diodes under res array Befehle are now smaler
2018-01-24 Footprints angeordnet
2018-01-24 units von U2 74541 organisieren
2018-01-24 Speichern vergessen ( jetzt nachgeholt)
2018-01-24 resistoren footprint ausgetsauscht (nicht fertig)
2018-01-26 library in .sch globalized
2018-01-26 tmpHermann aufgeräumt
2018-01-26 Akku Debug
2018-01-28 bugfixing
2018-01-31 Pcb layout
2018-01-31 problems solved and capacitors footprinted
2018-01-31 shizzl dizzl
2018-02-21 benennung der ICs
2018-02-21 textlabel für fehlende footprints in eintakt.sch added
2018-02-21 shizzl
2018-02-27 footprint IC1 ls624 VCO 14 pin
2018-02-27 footprint d1 smal diode do35 added
2018-02-27 todo Eintakt added
2018-02-27 ic1 vco lib problem solved
2018-02-27 falsches gehäuse ic1 vco
2018-02-27 todos eintakt done
2018-02-28 sym-lib-table hat sich wieder zurück gestellt
2018-02-28 TerminalBlocks hinzugefügt
2018-02-28 pcbTerminalBlockstg auch in pcb
2018-02-28 path exchange fixed
2018-02-28 Pcb layout und terminalblock 2
2018-02-28 Diode added, pins in 3erpins zusammengefasst, fehler beim speichern
2018-02-28 diode und erste pins
2018-03-21 Erste Leiterbahnen
2018-03-21 Pcb layout kabelverlegt
2018-03-21 Kabel gelegt
2018-03-27 Todo renamed
2018-03-29 Library Overwie added
2018-03-29 Schraub Anschlüsse zum Steuerwerk hinzugefügt
2018-03-29 Work on Libraries
2018-03-29 Schrauben Klemmen wegen library arbeit wieder entfernt
2018-03-29 Library Test put old Libs in bonsaicomplib
2018-03-29 74xx lib addet to bonsailib
2018-03-29 used libraries added
2018-03-30 library bugs solved (old libs renamed in project)
2018-03-30 moved global libraries tu project specific libraries
2018-03-30 forgotten vco Library moved
2018-03-30 doc to txt file
2018-03-30 terminal Blick renamed
2018-03-30 TerminalBlochTested
2018-04-01 Pin Header reorganized localy and adapted
2018-04-01 Didoe Footpront
2018-04-01 EintaktReset.todo done
2018-04-01 Befehle: Header ausgetauscht
2018-04-01 Befehle: Headers, Schraubkontakte Terminal Blocks, Kondensatoren eingefügt
2018-04-01 Speicher: Tip im todo.txt
2018-04-02 Steuerwerk: new smal LED custom lib and various bugfixes
2018-04-02 smal LED edinting
2018-04-02 smaller LEDs
2018-04-02 todo smaler LED done
2018-04-03 Switch Layer
2018-04-03 changed cupper front layer to bottom layer
2018-04-04 PCB layout revolutioniert
2018-04-04 weitere Leiterbahnen hinzugefügt
2018-04-04 pcb gelayoutet, Libraries benannt, todo.txt geändert!
2018-04-04 todo.txt geändert
2018-04-04 tracks gelegt
2018-04-11 Hilfen zu todos gegeben
2018-04-11 minimal änderungen
2018-04-11 wires gelegt
2018-04-11 Todo list dabei
2018-04-11 Verbindungen zum IC fortgeführt
2018-04-11 Text Datei zum Library Problem hinzugefügt
2018-04-11 todo aktualisiert und gelayoutet
2018-04-18 R2-R22 ausgetauscht und Buttons (footprints), todolist anglegt, Bauteile angeordnet (80%)
2018-04-18 pcb gelayoutet, footprint für capacitors geadded, 74ls32 teile zugeordnet, todo überarbeitet
2018-04-18 Leiterbahnen Korrigiert
2018-04-25 Library Datei zur ToDo Liste hinzugefügt
2018-04-25 ein einzelnes footprint geändert
2018-04-25 Weitere Leiterbahnen hinzugefügt und den überflüssigen IC entfernt
2018-04-25 KAel verlegt
2018-04-25 grobplazierung fertiggestellt, feinplatzierung angefangen
2018-04-25 tracks gelegt und so
2018-04-28 switch added
2018-04-28 mit Korrektur der Anordnung begonnen
2018-04-29 busses new arranged
2018-04-29 foodprint 2x10 Header size adjusted
2018-04-29 todos done (netze entflechten), some footprintslocaliszed
2018-05-02 Library für switches geadded
2018-05-02 Pcb layout viel weitergebracht
2018-05-02 wires gelegt und schamdoozels beseitigt
2018-05-02 neuer footprint für switch
2018-05-02 footprint problem behoben falsche todo list gelöscht etc.
2018-05-09 Butttons Neu
2018-05-09 Teile verschoben um mehr Platz zu kriegen
2018-05-09 Resistoren angepasst, switches geändert, sw6 braucht noch anpassung
2018-05-09 wires gelegt footprints getauscht
2018-05-22 eintakt modified
2018-05-30 austauschprozess
2018-05-30 Teile verschoben, bahnen verlängert, Teile geordnet
2018-05-30 mit libraryproblemen gedealt (teilweise erfolgreich), kabellegen angefangen
2018-05-30 Powerpins neu gemacht
2018-05-30 lololol fertig gg ez
2018-06-01 falsche ferbindung am lc374 korrigiert und rbussed eingefügt, condensatoren footprinted
2018-06-03 Pin Anordnung von 374 korrigiert, manche Fehler gefunden und Todo Liste erweitert
2018-06-13 Resistor Array system begonnen aber nicht alles connectors gefunden
2018-06-13 kleine LEDs auf ihren Platz gelegt
2018-06-13 bugs behoben
2018-06-13 Kabel links unten gelegt, Teile verschoben
2018-06-20 condensatoren eingefügt
2018-06-20 Teile geordnet und Notiz hinzugefügt
2018-06-20 bugs behoben und fertig gestellt
2018-06-20 tracks gelegt und aufkommende Fehler gelöst
2018-06-21 EinTaktReset: weiter Verbindungen gelegt, BUSCONNECTOR LINKS VERDREHT, todo updated
2018-06-21 EinTaktReset: Fehler in .sch behoben (Details in todo), Verbindungen großteils gelegt, todo updated
2018-06-22 EinTaktReset: Fehler behoben (Details in todo), PCB jetzt Fehlerfrei
2018-06-27 Letzte arbeit in der Stunde am 27.6.2018
2018-06-27 Überflüssige LEDs entfernt, 1k Resistoren Eingebaut, Teile geordnet
2018-06-27 footprint fertig ausgetauscht
2018-06-27 track width geändert
2018-12-31 libs
2019-01-02 generalized smlibtable
2019-01-03 Steuerwerk: a lot of things ...
2019-01-06 steuerwerk improvements
2019-01-07 tracs tracs tracs
2019-01-09 Steuerwerk wires finished
2019-01-13 overview and speicher
2019-01-19 works on speichermodul
2019-01-21 cleanup
2019-01-29 diverse Vorbereitungen für akku, switch update
2019-02-04 akku todos
2019-02-05 akku unit changing labeling rpack
2019-02-07 akku sch updates for same wireing in pcb
2019-02-07 akku wireing in pcb
2019-02-08 akku and wireing in pcb
2019-02-09 Akku pc finished
2019-02-10 Eintakt libs fixed
2019-02-10 Eintakt Buttons changed
2019-02-10 akku.neu and v4 cleanup
2019-02-10 big cleanup
2019-02-10 big cleanup 2
2019-02-11 big cleanup .sch files, symbols libs, project files
2019-02-11 BIB Cleanup finished
2019-02-11 Footprint Labes set invisible
2019-02-11 labeling
2019-02-11 branding
2019-04-05 druck optimierung
